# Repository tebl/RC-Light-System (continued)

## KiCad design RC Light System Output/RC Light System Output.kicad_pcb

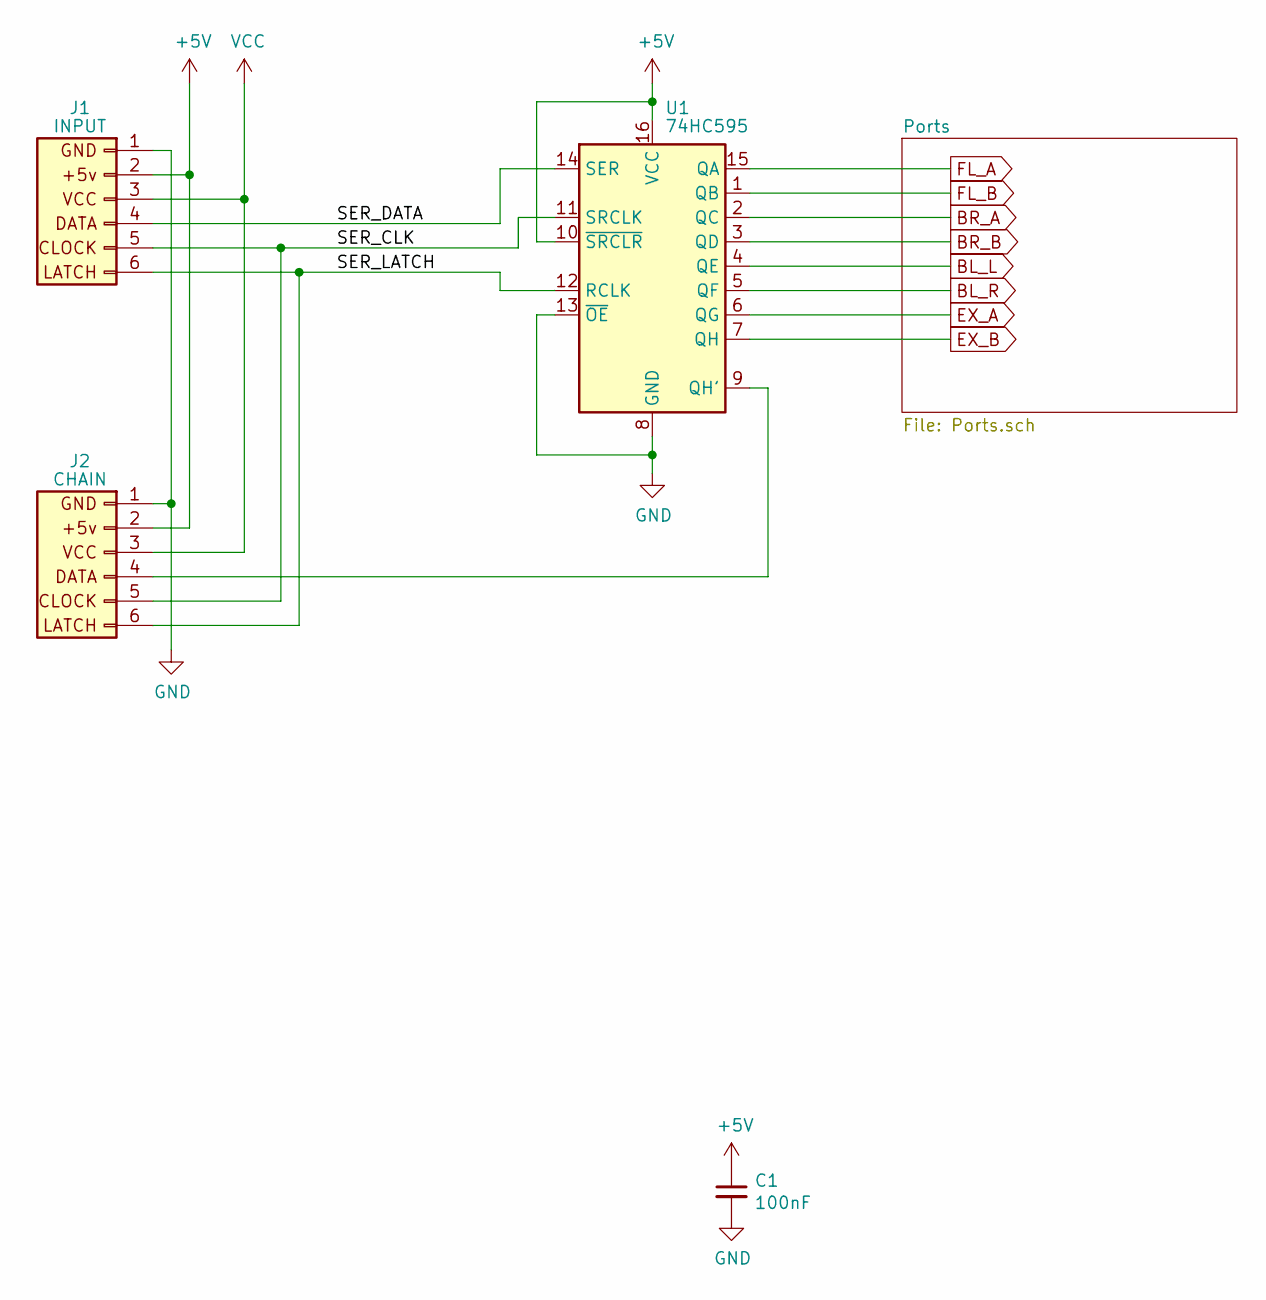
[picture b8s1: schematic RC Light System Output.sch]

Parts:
C1: 100nF; C_Disc_D4.7mm_W2.5mm_P5.00mm
J1: INPUT; JST_XH_B6B-XH-A_1x06_P2.50mm_Vertical
J2: CHAIN; JST_XH_B6B-XH-A_1x06_P2.50mm_Vertical
U1: 74HC595; DIP-16_W7.62mm_Socket_LongPads

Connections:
+5V: C1.1, J1.2 (+5V), J2.2 (+5V), U1.10 (~SRCLR), U1.16 (VCC)
/SER_CLK: J1.5 (CLOCK), J2.5 (CLOCK), U1.11 (SRCLK)
/SER_DATA: J1.4 (DATA), U1.14 (SER)
/SER_LATCH: J1.6 (LATCH), J2.6 (LATCH), U1.12 (RCLK)
BL_L: U1.4 (QE); also elsewhere on the board
BL_R: U1.5 (QF); also elsewhere on the board
BR_A: U1.2 (QC); also elsewhere on the board
BR_B: U1.3 (QD); also elsewhere on the board
EX_A: U1.6 (QG); also elsewhere on the board
EX_B: U1.7 (QH); also elsewhere on the board
FL_A: U1.15 (QA); also elsewhere on the board
FL_B: U1.1 (QB); also elsewhere on the board
GND: C1.2, J1.1 (GND), J2.1 (GND), U1.8 (GND), U1.13 (~OE); also elsewhere on the board
unnamed: J2.4 (DATA), U1.9 (QH')
VCC: J1.3 (VCC), J2.3 (VCC); also elsewhere on the board

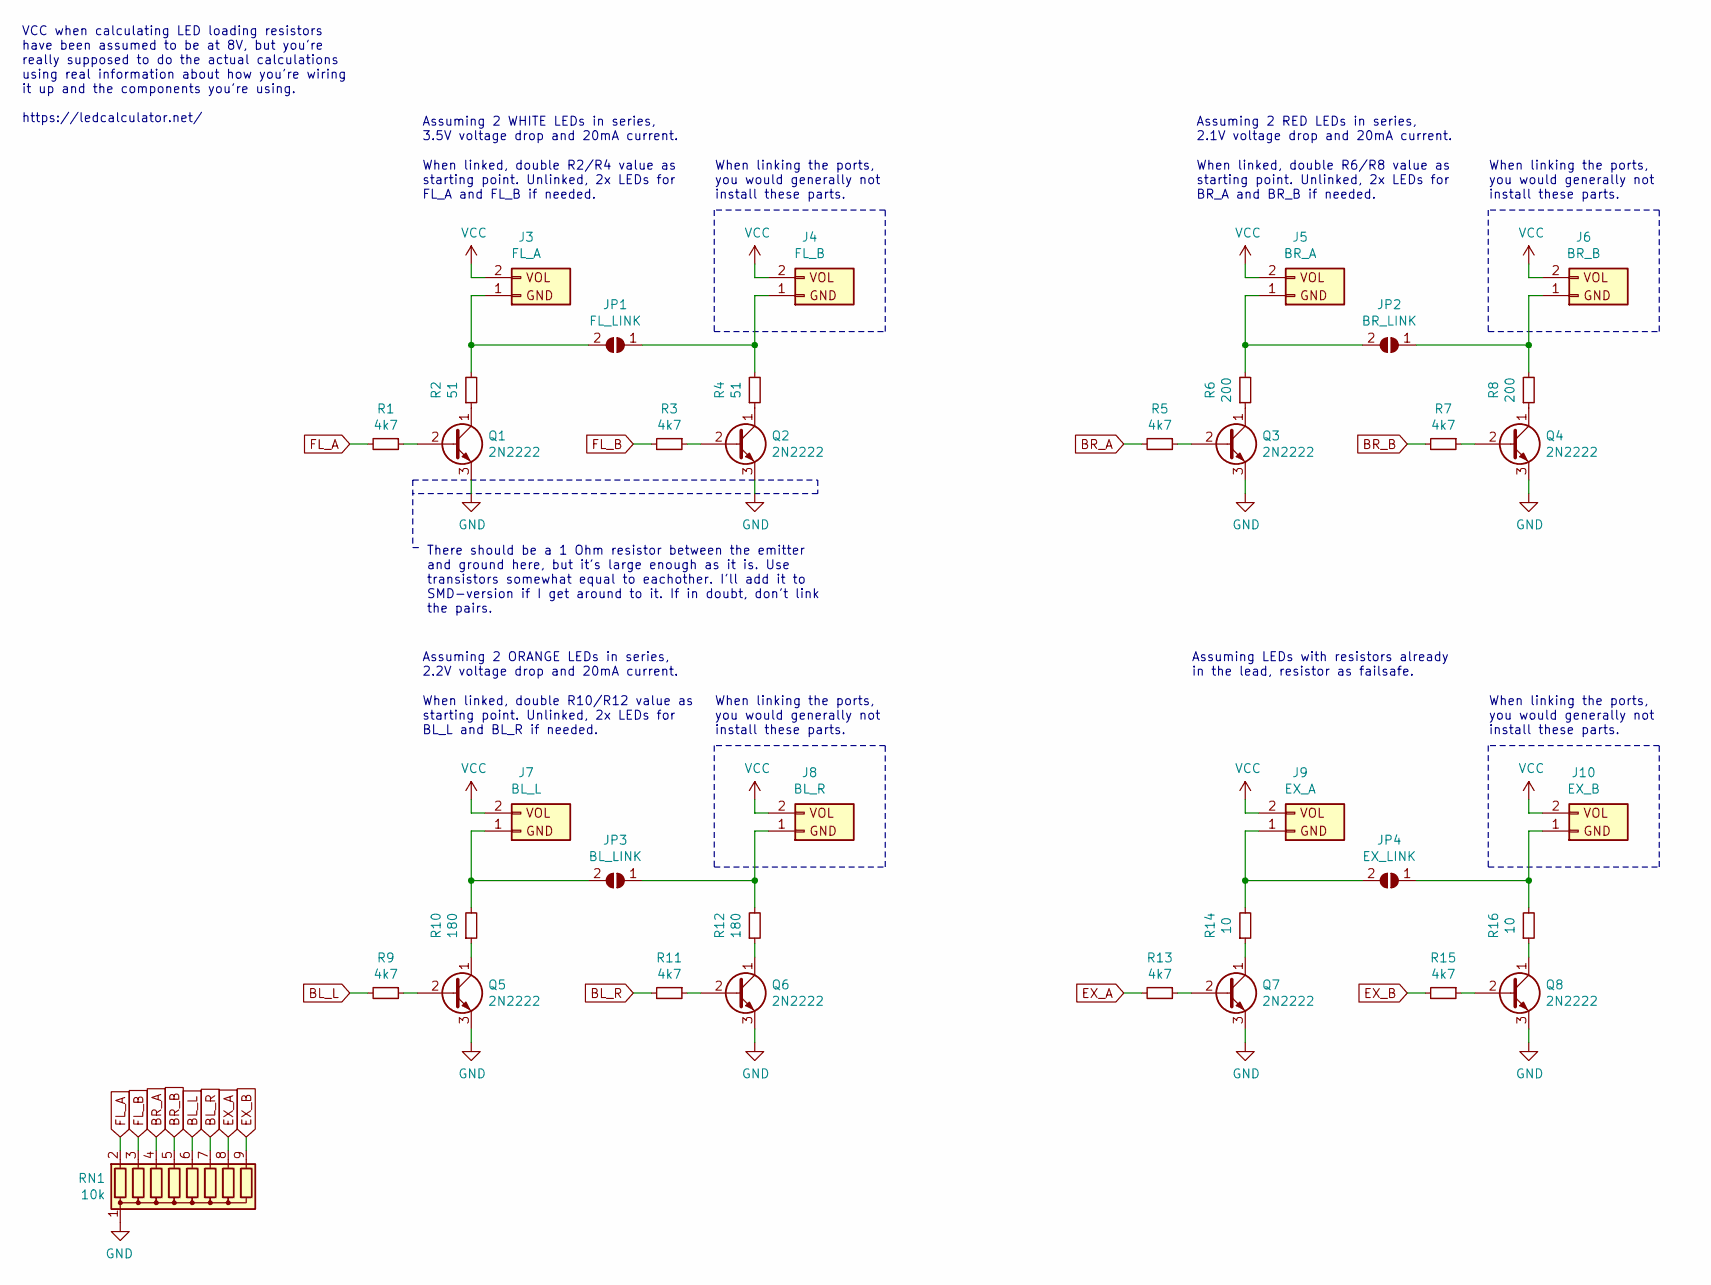
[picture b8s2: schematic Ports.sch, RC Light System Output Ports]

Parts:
J3: FL_A; JST_XH_B2B-XH-A_1x02_P2.50mm_Vertical
J4: FL_B; JST_XH_B2B-XH-A_1x02_P2.50mm_Vertical
J5: BR_A; JST_XH_B2B-XH-A_1x02_P2.50mm_Vertical
J6: BR_B; JST_XH_B2B-XH-A_1x02_P2.50mm_Vertical
J7: BL_L; JST_XH_B2B-XH-A_1x02_P2.50mm_Vertical
J8: BL_R; JST_XH_B2B-XH-A_1x02_P2.50mm_Vertical
J9: EX_A; JST_XH_B2B-XH-A_1x02_P2.50mm_Vertical
J10: EX_B; JST_XH_B2B-XH-A_1x02_P2.50mm_Vertical
JP1: FL_LINK; bridge_open
JP2: BR_LINK; bridge_open
JP3: BL_LINK; bridge_open
JP4: EX_LINK; bridge_open
Q1, Q2, Q3, Q4, Q5, Q6, Q7, Q8: 2N2222; TO-92_HandSolder
R1, R3, R5, R7, R9, R11, R13, R15: 4k7; R_Axial_DIN0207_L6.3mm_D2.5mm_P7.62mm_Horizontal
R2, R4: 51; R_Axial_DIN0207_L6.3mm_D2.5mm_P7.62mm_Horizontal
R6, R8: 200; R_Axial_DIN0207_L6.3mm_D2.5mm_P7.62mm_Horizontal
R10, R12: 180; R_Axial_DIN0207_L6.3mm_D2.5mm_P7.62mm_Horizontal
R14, R16: 10; R_Axial_DIN0207_L6.3mm_D2.5mm_P7.62mm_Horizontal
RN1: 10k; R_Array_SIP9

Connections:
BL_L: R9.2, RN1.6 (R5); also elsewhere on the board
BL_R: R11.2, RN1.7 (R6); also elsewhere on the board
BR_A: R5.2, RN1.4 (R3); also elsewhere on the board
BR_B: R7.2, RN1.5 (R4); also elsewhere on the board
EX_A: R13.2, RN1.8 (R7); also elsewhere on the board
EX_B: R15.2, RN1.9 (R8); also elsewhere on the board
FL_A: R1.2, RN1.2 (R1); also elsewhere on the board
FL_B: R3.2, RN1.3 (R2); also elsewhere on the board
GND: Q1.3 (E), Q2.3 (E), Q3.3 (E), Q4.3 (E), Q5.3 (E), Q6.3 (E), Q7.3 (E), Q8.3 (E), RN1.1 (common); also elsewhere on the board
unnamed: J3.1 (GND), JP1.2 (B), R2.2
unnamed: J4.1 (GND), JP1.1 (A), R4.2
unnamed: J5.1 (GND), JP2.2 (B), R6.2
unnamed: J6.1 (GND), JP2.1 (A), R8.2
unnamed: J7.1 (GND), JP3.2 (B), R10.2
unnamed: J8.1 (GND), JP3.1 (A), R12.2
unnamed: J9.1 (GND), JP4.2 (B), R14.2
unnamed: J10.1 (GND), JP4.1 (A), R16.2
unnamed: Q1.1 (C), R2.1
unnamed: Q1.2 (B), R1.1
unnamed: Q2.1 (C), R4.1
unnamed: Q2.2 (B), R3.1
unnamed: Q3.1 (C), R6.1
unnamed: Q3.2 (B), R5.1
unnamed: Q4.1 (C), R8.1
unnamed: Q4.2 (B), R7.1
unnamed: Q5.1 (C), R10.1
unnamed: Q5.2 (B), R9.1
unnamed: Q6.1 (C), R12.1
unnamed: Q6.2 (B), R11.1
unnamed: Q7.1 (C), R14.1
unnamed: Q7.2 (B), R13.1
unnamed: Q8.1 (C), R16.1
unnamed: Q8.2 (B), R15.1
VCC: J3.2 (+5V), J4.2 (+5V), J5.2 (+5V), J6.2 (+5V), J7.2 (+5V), J8.2 (+5V), J9.2 (+5V), J10.2 (+5V); also elsewhere on the board

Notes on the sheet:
When linking the ports, you would generally not install these parts.
Assuming 2 WHITE LEDs in series, 3.5V voltage drop and 20mA current.
When linked, double R2/R4 value as starting point. Unlinked, 2x LEDs for FL_A and FL_B if needed.
Assuming 2 RED LEDs in series, 2.1V voltage drop and 20mA current.
When linked, double R6/R8 value as starting point. Unlinked, 2x LEDs for BR_A and BR_B if needed.
Assuming 2 ORANGE LEDs in series, 2.2V voltage drop and 20mA current.
When linked, double R10/R12 value as starting point. Unlinked, 2x LEDs for BL_L and BL_R if needed.
VCC when calculating LED loading resistors have been assumed to be at 8V, but you're really supposed to do the actual calculations using real information about how you're wiring it up and the components you're using. https://ledcalculator.net/
Assuming LEDs with resistors already in the lead, resistor as failsafe.
There should be a 1 Ohm resistor between the emitter and ground here, but it's large enough as it is. Use transistors somewhat equal to eachother. I'll add it to SMD-version if I get around to it. If in doubt, don't link the pairs.

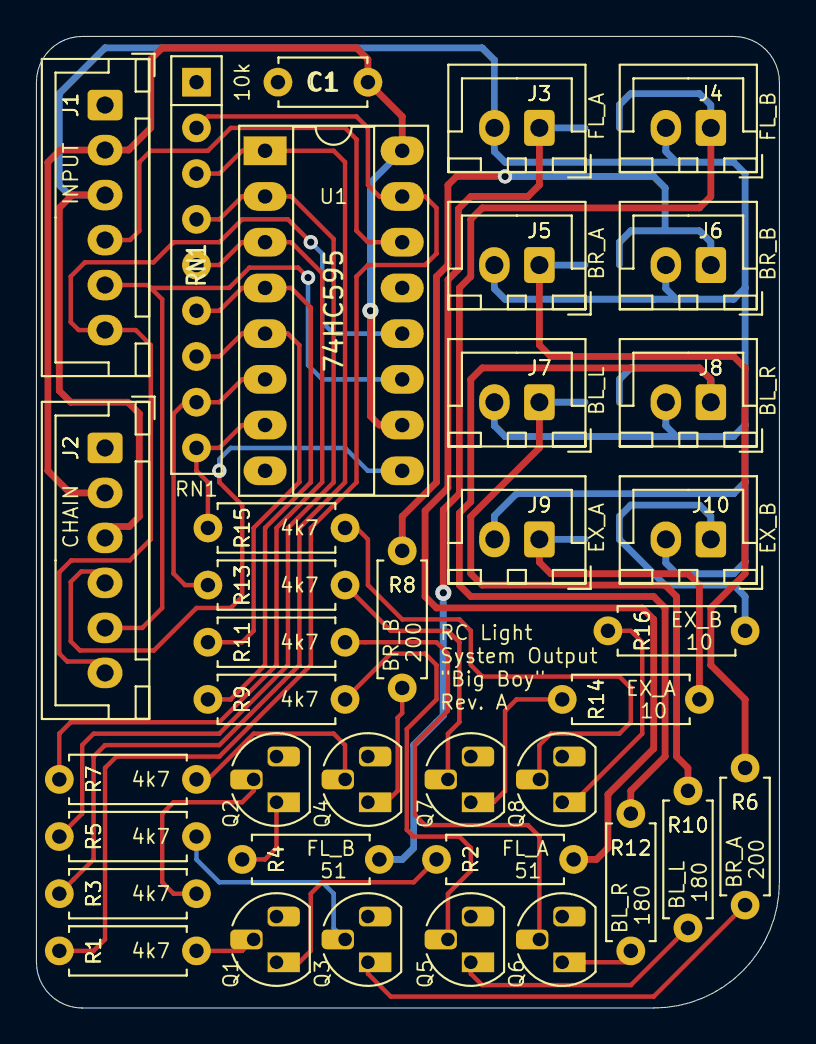
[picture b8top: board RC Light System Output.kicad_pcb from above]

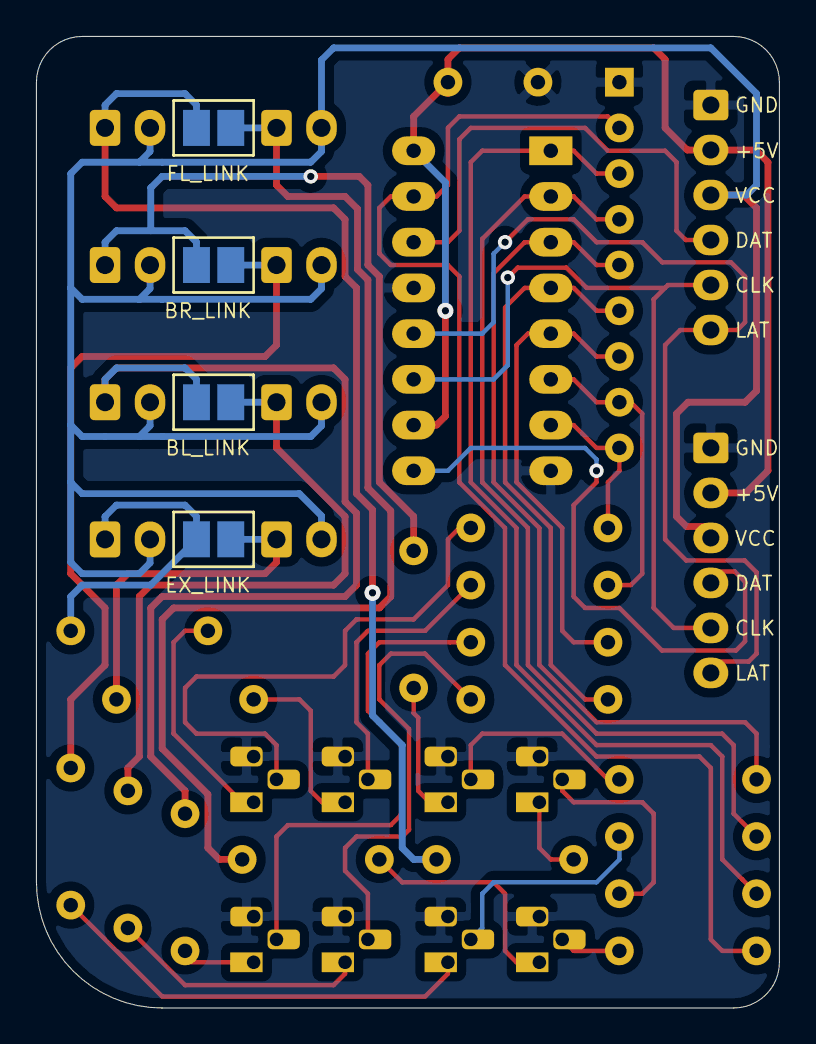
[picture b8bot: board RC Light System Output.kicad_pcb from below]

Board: 2 copper layers, 41.3 x 54.0 mm, 41 parts (4 on the bottom side), 39 nets.

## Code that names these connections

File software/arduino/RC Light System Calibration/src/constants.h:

#pragma once

#define PIN_THR 2
#define PIN_STR 3
#define SER_LATCH 4
#define SER_CLK_2 5
#define SER_CLK_1 7
#define SER_DATA 8
#define PIN_LED 17
#define PIN_AUX 18
#define PIN_VOL 21

/* These values need to be adjusted to the values used by your transmitter and
 * receiver combination. This is just starting points, the real values to use
 * with the lighting system will be output on the serial console.
 */
#define THROTTLE_PULSE_MIN 0
#define THROTTLE_PULSE_MAX 2500
#define STEERING_PULSE_MIN 0
#define STEERING_PULSE_MAX 2500

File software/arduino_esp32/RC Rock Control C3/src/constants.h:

#pragma once
#define PIN_CH1 20
#define PIN_CH2 10
#define PIN_LED_1 3
#define PIN_LED_2 2
#define PIN_LED_3 1
#define PIN_LED_4 0
#define PIN_CFG 7

#define LED_BUILTIN 8
#define PIN_BOOT 9

#define STATE_INVALID 0
#define STATE_IDLE 1
#define STATE_ACTIVE 2
#define STATE_NEGATIVE 2
#define STATE_POSITIVE 3

#define MODE_DISABLED 0
#define MODE_DYNAMIC 1
#define MODE_INVERTED 2
#define MODE_BREATHING 3
#define MODE_LOW 4
#define MODE_HIGH 5
#define MODE_LAST MODE_HIGH

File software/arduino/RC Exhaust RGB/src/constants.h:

#pragma once

#define PIN_THR 2
#define PIN_INT0 0  // INT0 is physically on PB2, so the same as above.
#define PIN_RGB_R 0
#define PIN_RGB_G 1
#define PIN_RGB_B 4

#define LED_OFF 0
#define LED_MIN LED_OFF

#define LED_NOTICE 32
#define LED_LOW 16
#define LED_MAX 255

#define GEAR_NEUTRAL 0
#define GEAR_DRIVE 1
#define GEAR_REVERSE 2
#define GEAR_PARKED 3

/* PWM with gamma correction, the usage of which were taken from an interesting
   article on https://www.arduinoslovakia.eu/blog/2018/8/attiny85---pwm?lang=en
   The effect is that smaller gradual changes are applied throughout the
   spectrum of in PWV values instead of appearing to be exponential with a peak
   quite a while before the actual maximum.

   As the article states, this was generated for values of i from 0 to 255 ->
     x=round( pow( 2.0, i/32.0) - 1);
*/
const byte gamma_values[] PROGMEM = {
  0,   0,   0,   0,   0,   0,   0,   0,   0,   0,   0,   0,   0,   0,   0,   0,
  0,   0,   0,   1,   1,   1,   1,   1,   1,   1,   1,   1,   1,   1,   1,   1,
  1,   1,   1,   1,   1,   1,   1,   1,   1,   1,   1,   2,   2,   2,   2,   2,
  2,   2,   2,   2,   2,   2,   2,   2,   2,   2,   3,   3,   3,   3,   3,   3,
  3,   3,   3,   3,   3,   3,   4,   4,   4,   4,   4,   4,   4,   4,   4,   5,
  5,   5,   5,   5,   5,   5,   5,   6,   6,   6,   6,   6,   6,   6,   7,   7,
  7,   7,   7,   8,   8,   8,   8,   8,   9,   9,   9,   9,   9,  10,  10,  10,
 10,  11,  11,  11,  11,  12,  12,  12,  12,  13,  13,  13,  14,  14,  14,  15,
 15,  15,  16,  16,  16,  17,  17,  18,  18,  18,  19,  19,  20,  20,  21,  21,
 22,  22,  23,  23,  24,  24,  25,  25,  26,  26,  27,  28,  28,  29,  30,  30,
 31,  32,  32,  33,  34,  35,  35,  36,  37,  38,  39,  40,  40,  41,  42,  43,
 44,  45,  46,  47,  48,  49,  51,  52,  53,  54,  55,  56,  58,  59,  60,  62,
 63,  64,  66,  67,  69,  70,  72,  73,  75,  77,  78,  80,  82,  84,  86,  88,
 90,  91,  94,  96,  98, 100, 102, 104, 107, 109, 111, 114, 116, 119, 122, 124,
127, 130, 133, 136, 139, 142, 145, 148, 151, 155, 158, 161, 165, 169, 172, 176,
180, 184, 188, 192, 196, 201, 205, 210, 214, 219, 224, 229, 234, 239, 244, 250
};

#define BACKFIRE_CYCLES 32

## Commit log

2023-08-10 Output schematic
2023-08-11 Map footprints and add transistor pulldowns
2023-08-12 Big boy output layout
2023-08-19 Control module schematic
2023-08-24 First layout done
2023-08-31 Exhaust module
2023-09-30 Added voltage dividers
2023-11-19 Printing THR
2023-11-19 Add STR value
2023-11-20 Set light according to THR (linked mode)
2023-11-26 Works some of the time, readings are glitched in some way
2023-11-27 Changed to a library, appears to function
2023-11-27 Normal running lights
2023-11-27 Doesn't park when we're standing still, but actively steering
2023-11-28 Moved some magic values into settings
2023-11-28 Added calibration sketch
2023-12-01 Exhaust as a digispark module
2023-12-01 Simplified power to use 5/6v
2023-12-05 Digispark dashboard sketch
2023-12-05 Document the weirdness before I forget
2023-12-07 Archive some designs as I probably won't keep working on them
2023-12-07 Dashboard module for Digispark
2023-12-09 Display some colour
2023-12-10 Add code to limit throttle bar display when in reverse
2023-12-10 Add alternate gear styling
2023-12-11 Of all the blinkyness, this one blinks the most
2024-02-05 Mini, though actually kind of huge, output module
2024-03-26 Small build tweaks to sizing and text
2024-03-28 Build images
2024-03-28 Add youtube image
2024-03-28 First incomplete README
2024-03-28 Say even more!
2024-06-23 Small exhaust tweaks to better fit Digistump into computers
2024-06-25 Commenting things
2024-06-25 Slightly tweak layout
2024-06-25 Exhaust README draft
2024-07-24 Trying out ESP32 C3
2024-07-24 Cleanup
2024-07-25 Change to ServoInput and move project
2024-07-26 SuperMini board
2024-07-26 Boot image shown when not connected
2024-08-02 Small build tweaks
2024-08-02 Adding a delay fixes u8g2 startup issue???
2024-08-03 Preparing for the next thing
2024-08-04 SuperMini2, same as the old one except bigger and has two LED channels
2024-08-12 Confusing myself by generalizing channel names
2024-11-11 Add a couple of LED-channels
2024-11-12 Blink LEDs
2024-11-13 SuperMini2
2024-11-13 SCX10.3 Rock lights
2024-11-13 Use ch1 to control headlights
2024-11-15 Sort of works
2024-11-16 Some simple modes
2024-11-17 LEDs make more sense
2024-11-17 Slight build tweaks
2024-11-17 Missing track
2024-11-17 One-channel inverted mode
2024-11-17 Added steering to inverted mode
2024-11-18 Dynamic value linked to other LED, not channel
2024-11-18 Make it easier to fit diode the right way around
